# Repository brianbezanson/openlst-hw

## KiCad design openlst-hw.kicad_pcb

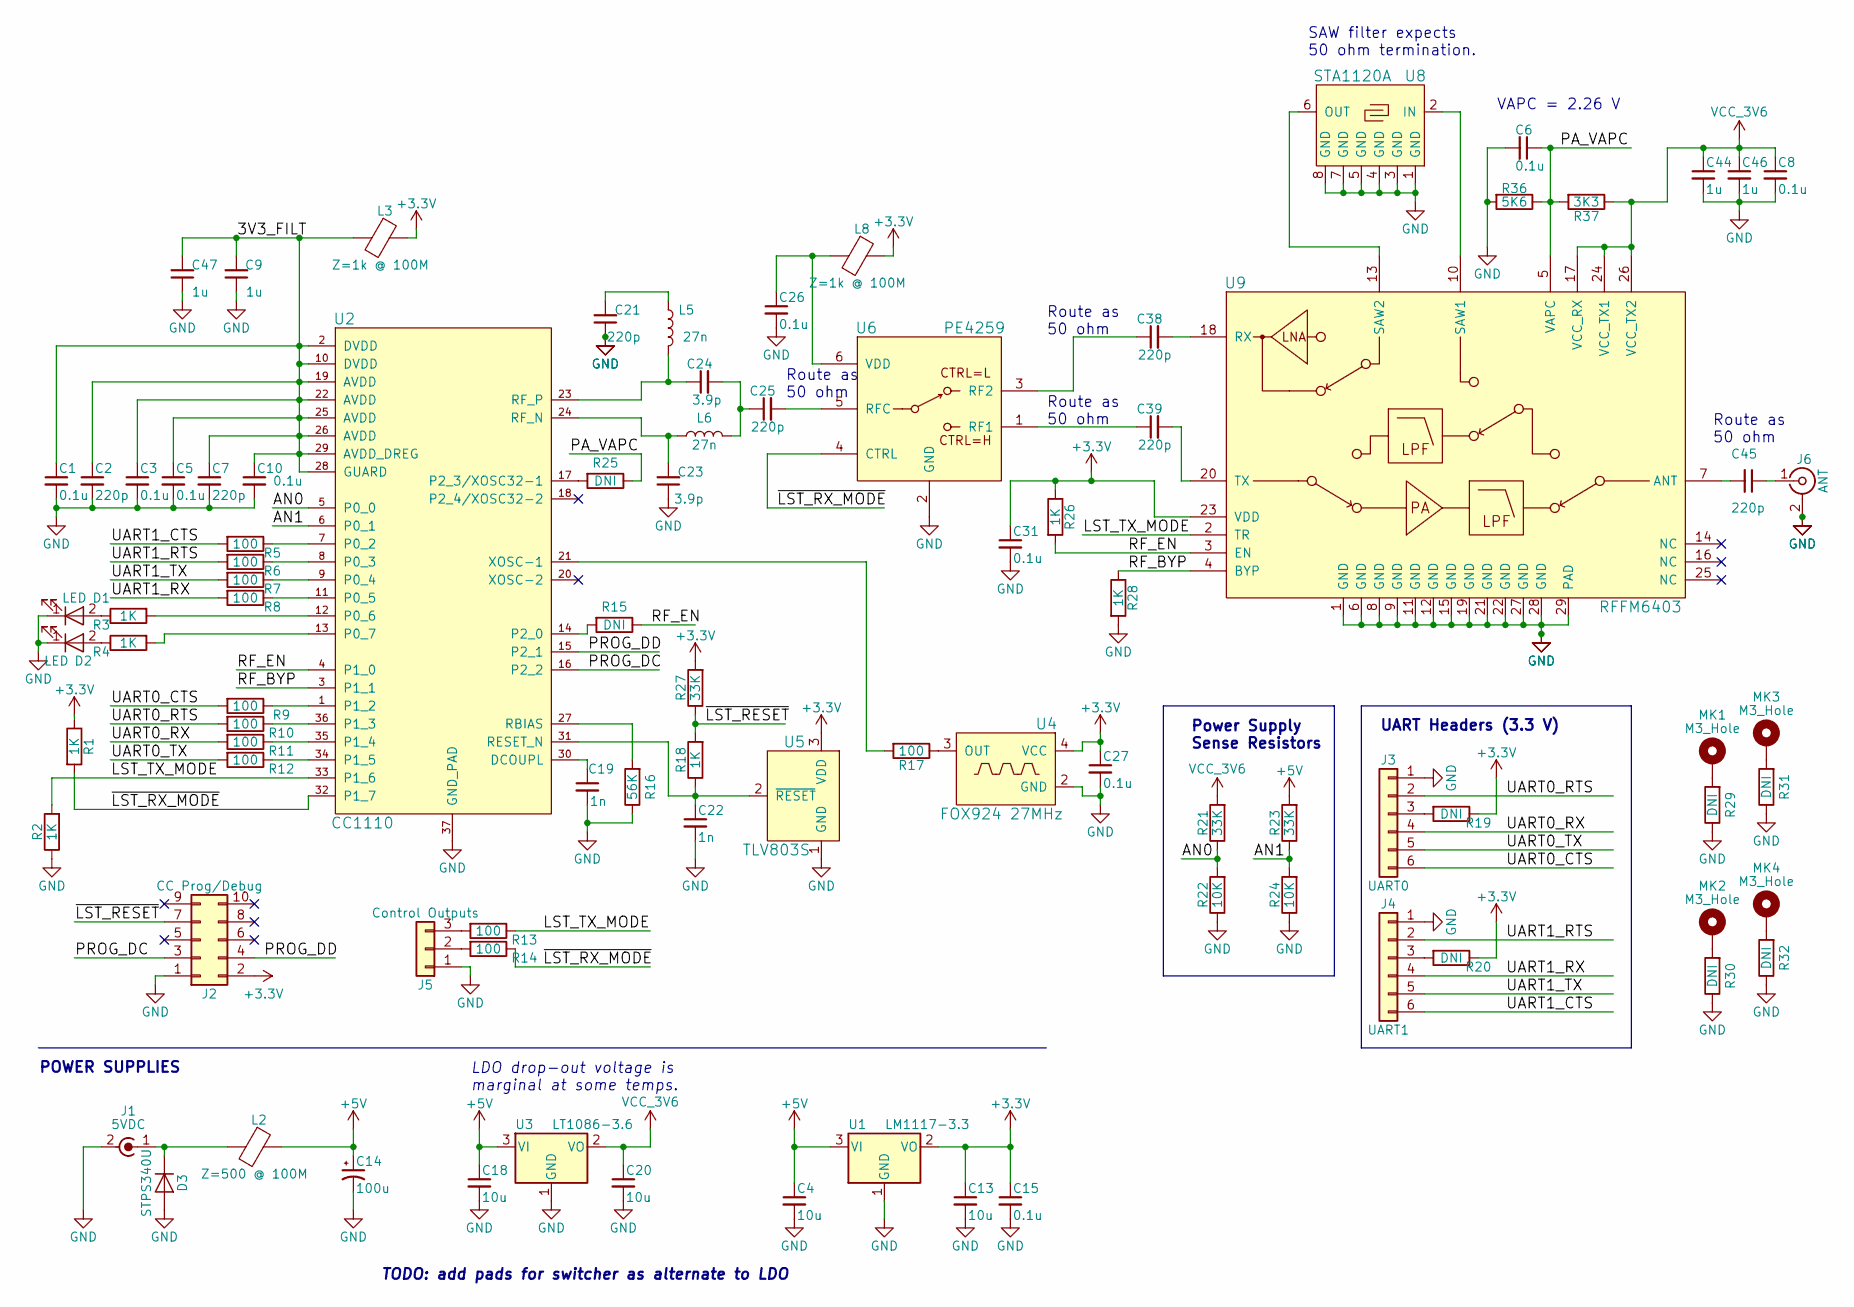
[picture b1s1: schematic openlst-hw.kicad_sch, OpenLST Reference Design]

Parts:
C1, C3, C5, C6, C8, C10, C15, C26, C27, C31: 0.1u; C_0603_1608Metric; ManufPN 0603YC104K4T4A
C2, C7, C21, C25, C38, C39, C45: 220p; C_0402_1005Metric; ManufPN C0402C221J2GACAUTO
C4, C13, C18, C20: 10u; C_0603_1608Metric; ManufPN GRT188C81A106ME13D
C9, C44, C46, C47: 1u; C_0603_1608Metric; ManufPN CL10B105MO8NNWC
C14: 100u; CP_EIA-3528-15_AVX-H; ManufPN TPSB107M010R0400
C19, C22: 1n; C_0603_1608Metric; ManufPN GCM188R71E102KA37D
C23, C24: 3.9p; C_0402_1005Metric; ManufPN GJM1555C1H3R9CB01D
D1: LED; LED_0603_1608Metric; ManufPN 150060VS75000
D2: LED; LED_0603_1608Metric; ManufPN 150060SS75000
D3: STPS340U; D_SMB; ManufPN STPS340U
J1: 5VDC; PinHeader_1x02_P2.54mm_Vertical
J2: CC Prog/Debug; PinHeader_2x05_P1.27mm_Vertical_SMD; ManufPN FTSH-105-01-L-DV-K-P
J3: UART0; PinHeader_1x06_P2.54mm_Vertical; ManufPN 61300611121
J4: UART1; PinHeader_1x06_P2.54mm_Vertical; ManufPN 61300611121
J5: Control Outputs; PinHeader_1x03_P2.54mm_Vertical
J6: ANT; SMA_Molex_73251-1153_EdgeMount_Horizontal; ManufPN 732511150
L2: Z=500 @ 100M; L_1206_3216Metric; ManufPN MI1206L501R-10
L3, L8: Z=1k @ 100M; L_0603_1608Metric; ManufPN 74279266
L5, L6: 27n; L_0402_1005Metric; ManufPN LQW15AN27NJ00D
MK1, MK2, MK3, MK4: M3_Hole; MountingHole_3.2mm_M3_Pad_Via
R1, R2, R3, R4, R18, R26, R28: 1K; R_0603_1608Metric; ManufPN RC0603JR-071KL
R5, R6, R7, R8, R9, R10, R11, R12, R13, R14, R17: 100; R_0603_1608Metric; ManufPN AC0603FR-07100RL
R15, R19, R20, R25, R29, R30, R31, R32: DNI; R_0603_1608Metric
R16: 56K; R_0603_1608Metric; ManufPN RMCF0603FT56K0
R21, R23, R27: 33K; R_0603_1608Metric; ManufPN AC0603FR-0733KL
R22, R24: 10K; R_0603_1608Metric; ManufPN RC0603JR-0710KL
R36: 5K6; R_0603_1608Metric; ManufPN RMCF0603FT5K60
R37: 3K3; R_0603_1608Metric; ManufPN RMCF0603FT3K30
U1: LM1117-3.3; SOT-223-3_TabPin2; ManufPN LM1117IMP-3.3/NOPB
U2: CC1110; TI_CC_QFN36; ManufPN CC1110F32RHHR
U3: LT1086-3.6; TO-263-3_TabPin2; ManufPN LT1086CM-3.6#PBF
U4: FOX924 27MHz; Oscillator_SMD_Fordahl_DFAS15-4Pin_5.0x3.2mm; ManufPN FT5HNBPK27.0-T1
U5: TLV803S; SOT-23; ManufPN TLV803SDBZR
U6: PE4259; SOT-363_SC-70-6; ManufPN 4259-63
U8: STA1120A; SAW-8_3.8mm; ManufPN STA1120A
U9: RFFM6403; Qorvo_LGA_28_ThermalVias; ManufPN RFFM6403SB

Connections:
+3V3: C13.1, C15.1, C27.1, C31.1, J2.2, L3.1, L8.1, R1.1, R19.1, R20.1, R26.1, R27.2, U1.2 (VO), U4.4 (VCC), U5.3 (VDD), U9.23 (VDD)
+5V: C4.1, C14.1, C18.1, L2.1, R23.2, U1.3 (VI), U3.3 (VI)
/3V3_FILT: C1.1, C2.1, C3.1, C5.1, C7.1, C9.2, C10.1, C47.2, L3.2, U2.2 (DVDD), U2.10 (DVDD), U2.19 (AVDD), U2.22 (AVDD), U2.25 (AVDD), U2.26 (AVDD), U2.28 (GUARD), U2.29 (AVDD_DREG)
/AN0: R21.1, R22.2, U2.5 (P0_0)
/AN1: R23.1, R24.2, U2.6 (P0_1)
/LST_TX_MODE: R2.2, R13.1, U2.33 (P1_6), U9.2 (TR)
/PA_VAPC: C6.1, R25.1, R36.1, R37.2, U9.5 (VAPC)
/PROG_DC: J2.3, U2.16 (P2_2)
/PROG_DD: J2.4, U2.15 (P2_1)
/RF_BYP: R28.1, U2.3 (P1_1), U9.4 (BYP)
/RF_EN: R15.1, R26.2, U2.4 (P1_0), U9.3 (EN)
/UART0_CTS: J3.6, R9.2
/UART0_RTS: J3.2, R10.2
/UART0_RX: J3.4, R11.2
/UART0_TX: J3.5, R12.2
/UART1_CTS: J4.6, R5.2
/UART1_RTS: J4.2, R6.2
/UART1_RX: J4.4, R8.2
/UART1_TX: J4.5, R7.2
/~LST_RESET: J2.7, R18.2, R27.1
/~LST_RX_MODE: R1.2, R14.1, U2.32 (P1_7), U6.4 (CTRL)
GND: C1.2, C2.2, C3.2, C4.2, C5.2, C6.2, C7.2, C8.2, C9.1, C10.2, C13.2, C14.2, C15.2, C18.2, C19.2, C20.2, C21.1, C22.2, C23.1, C26.2, C27.2, C31.2, C44.2, C46.2, C47.1, D1.1 (K), D2.1 (K), D3.2 (A), J1.2 (Ext), J2.1, J3.1, J4.1, J5.1, J6.2 (Ext), R2.1, R16.1, R22.1, R24.1, R28.2, R29.1, R30.1, R31.1, R32.1, R36.2, U1.1 (GND), U2.37 (GND_PAD), U3.1 (GND), U4.2 (GND), U5.1 (GND), U6.2 (GND), U8.1 (GND), U8.3 (GND), U8.4 (GND), U8.5 (GND), U8.7 (GND), U8.8 (GND), U9.1 (GND), U9.6 (GND), U9.8 (GND), U9.9 (GND), U9.11 (GND), U9.12 (GND), U9.15 (GND), U9.19 (GND), U9.21 (GND), U9.22 (GND), U9.27 (GND), U9.28 (GND), U9.29 (PAD)
unnamed: C19.1, U2.30 (DCOUPL)
unnamed: C21.2, L5.1
unnamed: C22.1, R18.1, U2.31 (RESET_N), U5.2 (~RESET)
unnamed: C23.2, L6.1, U2.24 (RF_N)
unnamed: C24.1, L5.2, U2.23 (RF_P)
unnamed: C24.2, C25.1, L6.2
unnamed: C25.2, U6.5 (RFC)
unnamed: C26.1, L8.2, U6.6 (VDD)
unnamed: C38.1, U6.3 (RF2)
unnamed: C38.2, U9.18 (RX)
unnamed: C39.1, U6.1 (RF1)
unnamed: C39.2, U9.20 (TX)
unnamed: C45.1, J6.1 (In)
unnamed: C45.2, U9.7 (ANT)
unnamed: D1.2 (A), R3.1
unnamed: D2.2 (A), R4.1
unnamed: D3.1 (K), J1.1 (In), L2.2
unnamed: J3.3, R19.2
unnamed: J4.3, R20.2
unnamed: J5.2, R14.2
unnamed: J5.3, R13.2
unnamed: MK1.1, R29.2
unnamed: MK2.1, R30.2
unnamed: MK3.1, R31.2
unnamed: MK4.1, R32.2
unnamed: R3.2, U2.12 (P0_6)
unnamed: R4.2, U2.13 (P0_7)
unnamed: R5.1, U2.7 (P0_2)
unnamed: R6.1, U2.8 (P0_3)
unnamed: R7.1, U2.9 (P0_4)
unnamed: R8.1, U2.11 (P0_5)
unnamed: R9.1, U2.1 (P1_2)
unnamed: R10.1, U2.36 (P1_3)
unnamed: R11.1, U2.35 (P1_4)
unnamed: R12.1, U2.34 (P1_5)
unnamed: R15.2, U2.14 (P2_0)
unnamed: R16.2, U2.27 (RBIAS)
unnamed: R17.1, U4.3 (OUT)
unnamed: R17.2, U2.21 (XOSC-1)
unnamed: R25.2, U2.17 (P2_3/XOSC32-1)
unnamed: U8.2 (IN), U9.10 (SAW1)
unnamed: U8.6 (OUT), U9.13 (SAW2)
VCC_3V6: C8.1, C20.1, C44.1, C46.1, R21.2, R37.1, U3.2 (VO), U9.17 (VCC_RX), U9.24 (VCC_TX1), U9.26 (VCC_TX2)

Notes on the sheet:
TODO: add pads for switcher as alternate to LDO
Route as 50 ohm
UART Headers (3.3 V)
POWER SUPPLIES
SAW filter expects 50 ohm termination.
Power Supply Sense Resistors
VAPC = 2.26 V
LDO drop-out voltage is marginal at some temps.

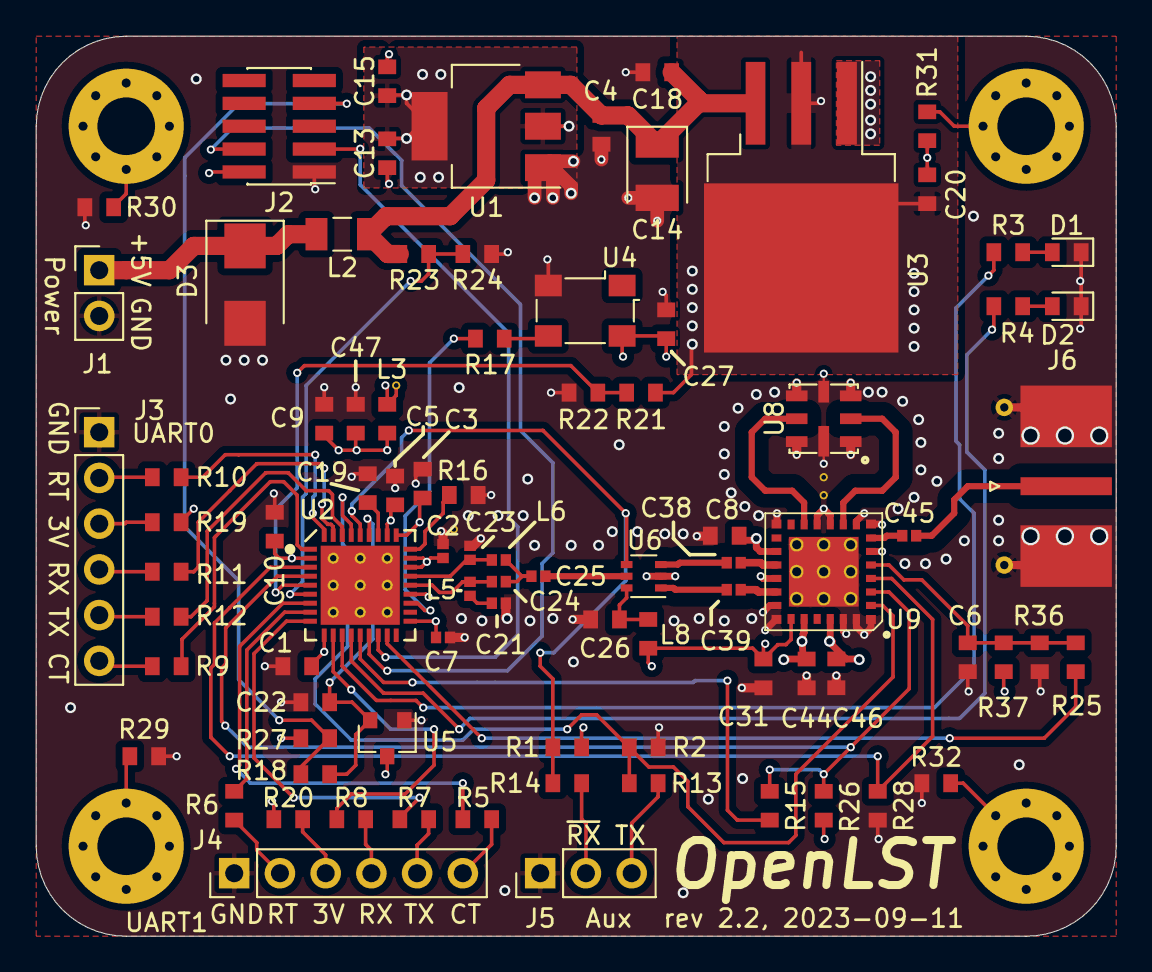
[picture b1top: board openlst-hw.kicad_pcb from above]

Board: 4 copper layers, 60.0 x 50.0 mm, 90 parts (0 on the bottom side), 65 nets.

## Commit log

2023-09-11 Migrate to KiCad 7 files, schematic visual cleanup, pcb routing cleanup
2023-09-11 DRC cleanup
2023-09-11 Beef up PA thermal vias
2023-09-11 Replace stitching pads with vias, add top ground fill
2023-09-12 Adjust SMA pads and board setup
2023-09-13 Silkscreen labels for UART pins

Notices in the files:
openlst-hw.kicad_pcb:
This work is licensed under a
Creative Commons Attribution-ShareAlike 4.0
International License (CC-BY-SA 4.0).
openlst-hw.kicad_sch:
This work is licensed under a Creative Commons Attribution-ShareAlike 4.0 International
Copyright 2018 Planet Labs Inc
